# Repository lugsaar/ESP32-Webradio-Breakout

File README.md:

# ESP32-Webradio-SMT

This project is a basic board to build an ESP32 webradio. This is the very compact SMT variant. As an idea we used a
[blog article](https://www.az-delivery.de/blogs/azdelivery-blog-fur-arduino-und-raspberry-pi/internet-radio-mit-dem-esp32) 
of the company AZ-Delivery in March 2022. You will need some better SMT soldering skills.

## technical details

coming later

## current state

## maintained

- [Dominik](mailto:dominik@lug-saar.de) (LUG-Saar)
- [Manfred](mailto:mancas@lug-saar.de) (LUG-Saar)
- [Thomas](mailto:mase@setho.org) (TKS)

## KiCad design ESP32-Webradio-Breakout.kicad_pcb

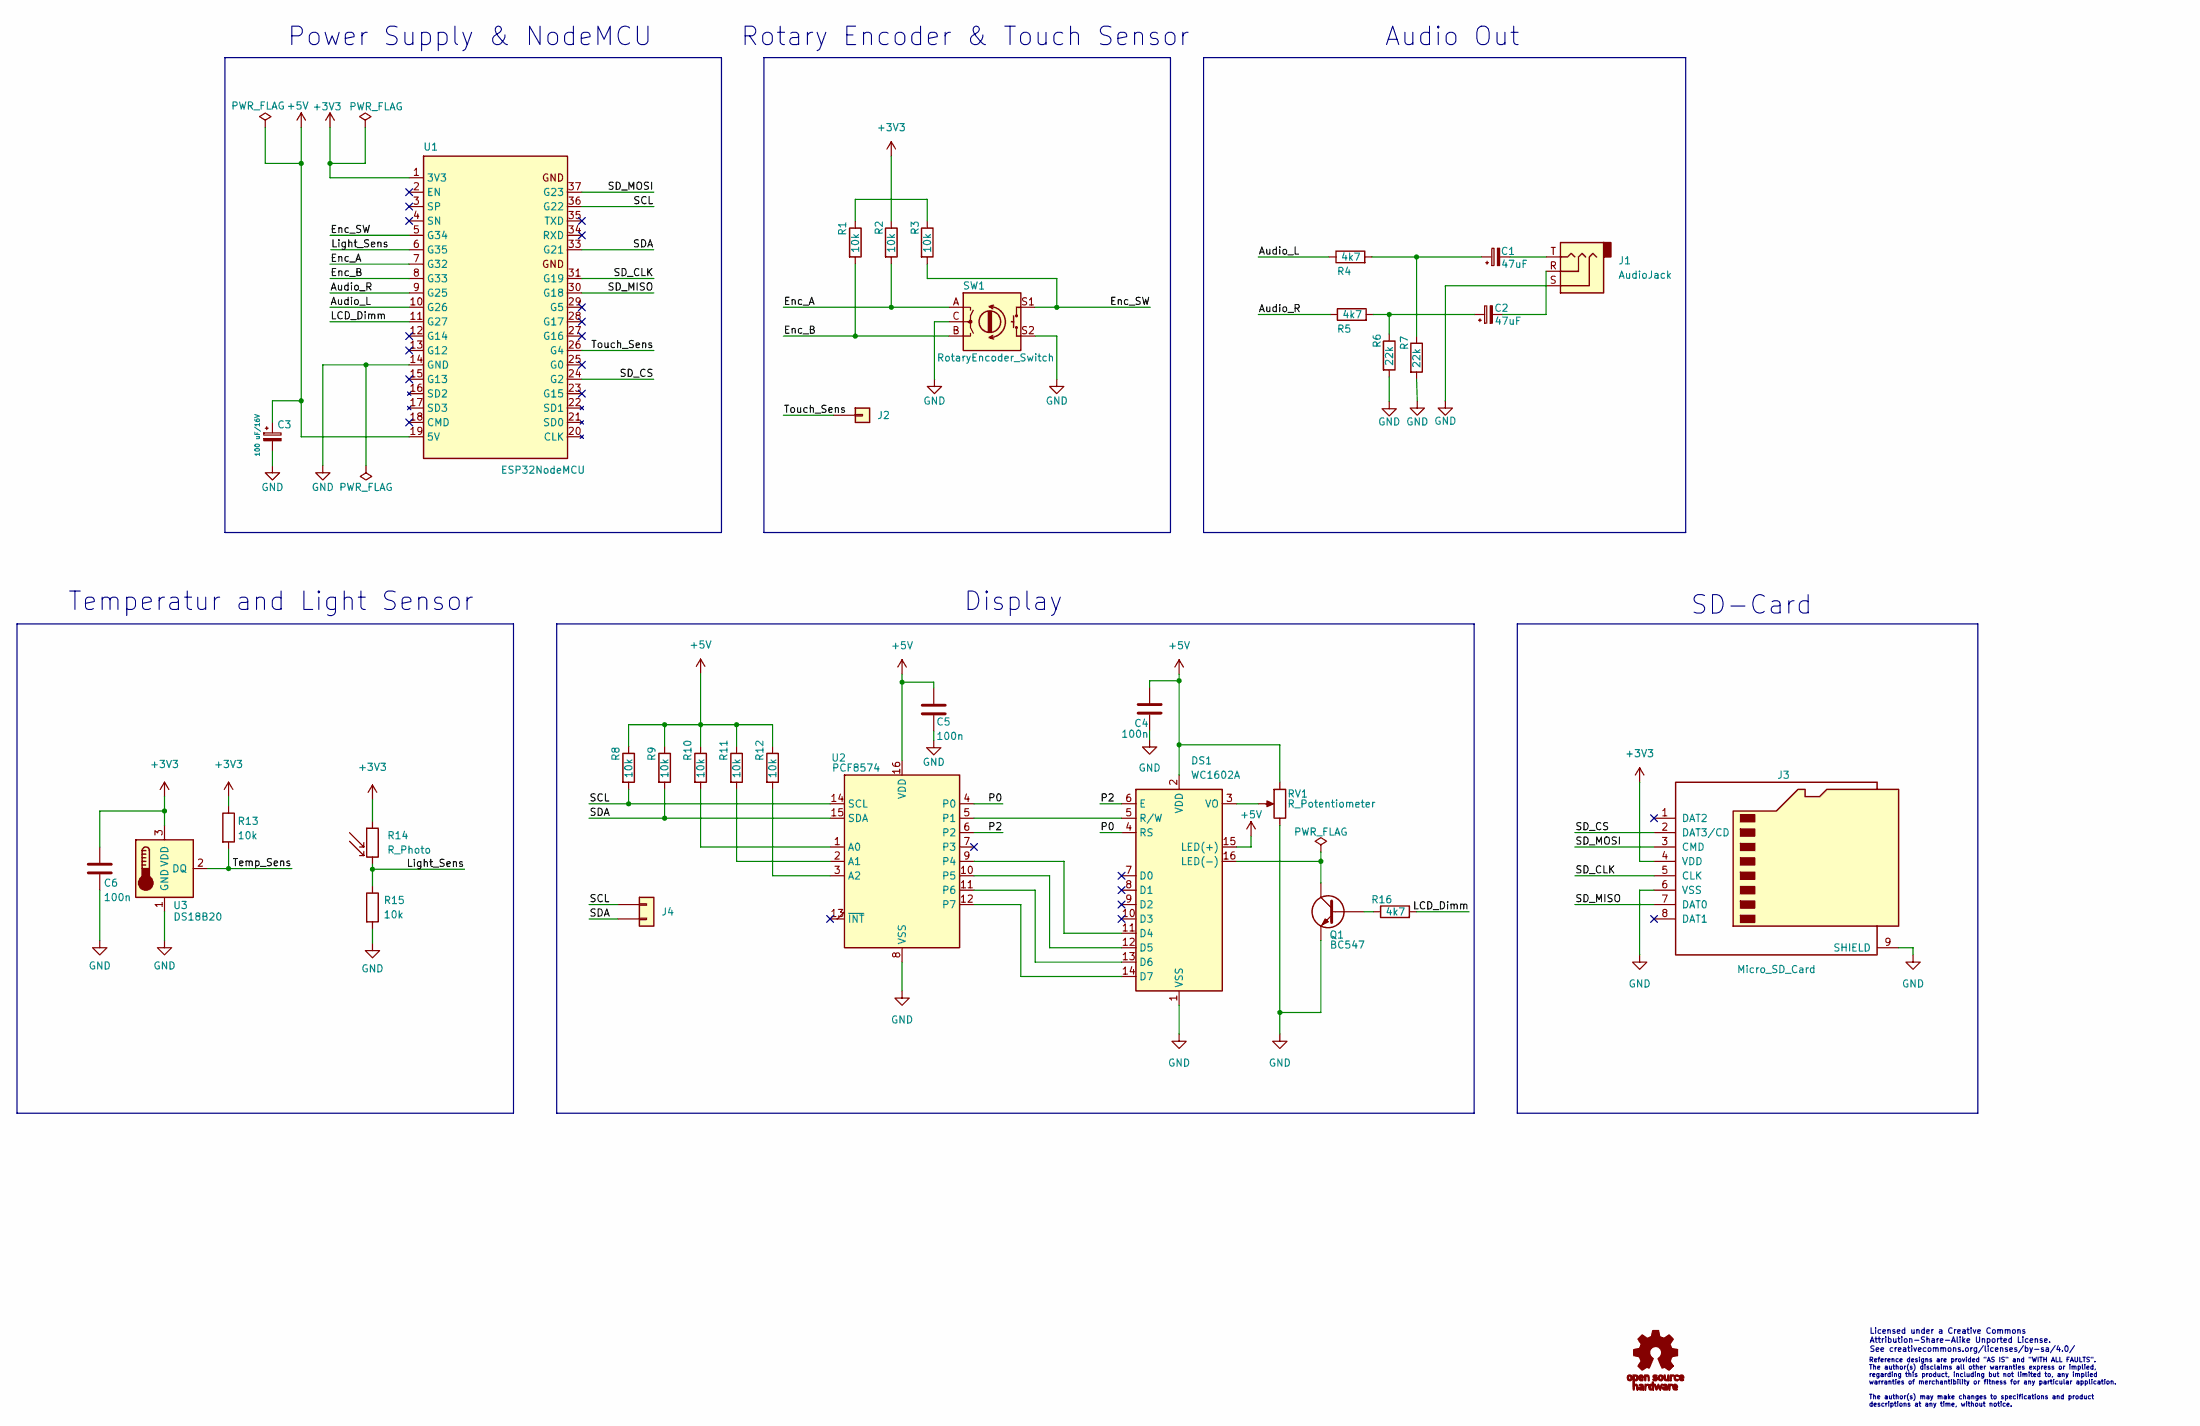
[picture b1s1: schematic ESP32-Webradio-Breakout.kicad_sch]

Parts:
C1, C2: 47uF; CP_Radial_D5.0mm_P2.50mm
C3: 100 uF/16V; CP_Radial_D6.3mm_P2.50mm
C4, C5, C6: 100n; C_Rect_L7.0mm_W3.5mm_P5.00mm
DS1: WC1602A; PinHeader_1x16_P2.54mm_Vertical
J1: AudioJack; Jack_3.5mm_CUI_SJ1-3533NG_Horizontal
J2: Conn_01x01; PinHeader_1x01_P2.54mm_Vertical
J3: Micro_SD_Card; PinHeader_1x08_P2.54mm_Vertical
J4: Conn_01x02; PinHeader_1x02_P2.54mm_Vertical
Q1: BC547; TO-92_Inline
R1, R2, R3, R8, R9, R10, R11, R12, R13, R15: 10k; R_Axial_DIN0207_L6.3mm_D2.5mm_P10.16mm_Horizontal
R4, R5, R16: 4k7; R_Axial_DIN0207_L6.3mm_D2.5mm_P10.16mm_Horizontal
R6, R7: 22k; R_Axial_DIN0207_L6.3mm_D2.5mm_P10.16mm_Horizontal
R14: R_Photo; R_LDR_5.1x4.3mm_P3.4mm_Vertical
RV1: R_Potentiometer; Potentiometer_ACP_CA9-V10_Vertical_Hole
SW1: RotaryEncoder_Switch; RotaryEncoder_Alps_EC11E-Switch_Vertical_H20mm
U1: ESP32NodeMCU; ESP32-NodeMCU_WROOM_32
U2: PCF8574; DIP-16_W10.16mm_LongPads
U3: DS18B20; TO-92_Inline

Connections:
+3V3: C6.1, J3.4 (VDD), R2.1, R13.1, R14.1, U1.1 (3V3), U3.3 (VDD)
+5V: C3.1, C4.1, C5.1, DS1.2 (VDD), DS1.15 (LED(+)), R8.1, R9.1, R10.1, R11.1, R12.1, RV1.1, U1.19 (5V), U2.16 (VDD)
/Audio_L: R4.1, U1.10 (G26)
/Audio_R: R5.1, U1.9 (G25)
/Enc_A: R2.2, SW1.A, U1.7 (G32)
/Enc_B: R1.2, SW1.B, U1.8 (G33)
/Enc_SW: R3.2, SW1.S1, U1.5 (G34)
/LCD_Dimm: R16.2, U1.11 (G27)
/Light_Sens: R14.2, R15.1, U1.6 (G35)
/P0: DS1.4 (RS), U2.4 (P0)
/P2: DS1.6 (E), U2.6 (P2)
/SCL: J4.1, R8.2, U1.36 (G22), U2.14 (SCL)
/SDA: J4.2, R9.2, U1.33 (G21), U2.15 (SDA)
/SD_CLK: J3.5 (CLK), U1.31 (G19)
/SD_CS: J3.2 (DAT3/CD), U1.24 (G2)
/SD_MISO: J3.7 (DAT0), U1.30 (G18)
/SD_MOSI: J3.3 (CMD), U1.37 (G23)
/Temp_Sens: R13.2, U3.2 (DQ)
/Touch_Sens: J2.1, U1.26 (G4)
GND: C3.2, C4.2, C5.2, C6.2, DS1.1 (VSS), J1.S, J3.6 (VSS), J3.9 (SHIELD), Q1.3 (E), R6.2, R7.2, R15.2, RV1.3, SW1.C, SW1.S2, U1.14 (GND), U1.32 (GND), U1.38 (GND), U2.8 (VSS), U3.1 (GND)
unnamed: C1.1, R4.2, R7.1
unnamed: C1.2, J1.T
unnamed: C2.1, R5.2, R6.1
unnamed: C2.2, J1.R
unnamed: DS1.3 (VO), RV1.2
unnamed: DS1.5 (R/W), U2.5 (P1)
unnamed: DS1.11 (D4), U2.9 (P4)
unnamed: DS1.12 (D5), U2.10 (P5)
unnamed: DS1.13 (D6), U2.11 (P6)
unnamed: DS1.14 (D7), U2.12 (P7)
unnamed: DS1.16 (LED(-)), Q1.1 (C)
unnamed: Q1.2 (B), R16.1
unnamed: R1.1, R3.1
unnamed: R10.2, U2.1 (A0)
unnamed: R11.2, U2.2 (A1)
unnamed: R12.2, U2.3 (A2)

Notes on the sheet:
Display
Licensed under a Creative Commons Attribution-Share-Alike Unported License. See creativecommons.org/licenses/by-sa/4.0/
Reference designs are provided "AS IS" and "WITH ALL FAULTS". The author(s) disclaims all other warranties express or implied, regarding this product, including but not limited to, any implied warranties of merchantibility or fitness for any particular application. The author(s) may make changes to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
Temperatur and Light Sensor
SD-Card
Power Supply & NodeMCU
Rotary Encoder & Touch Sensor
Audio Out

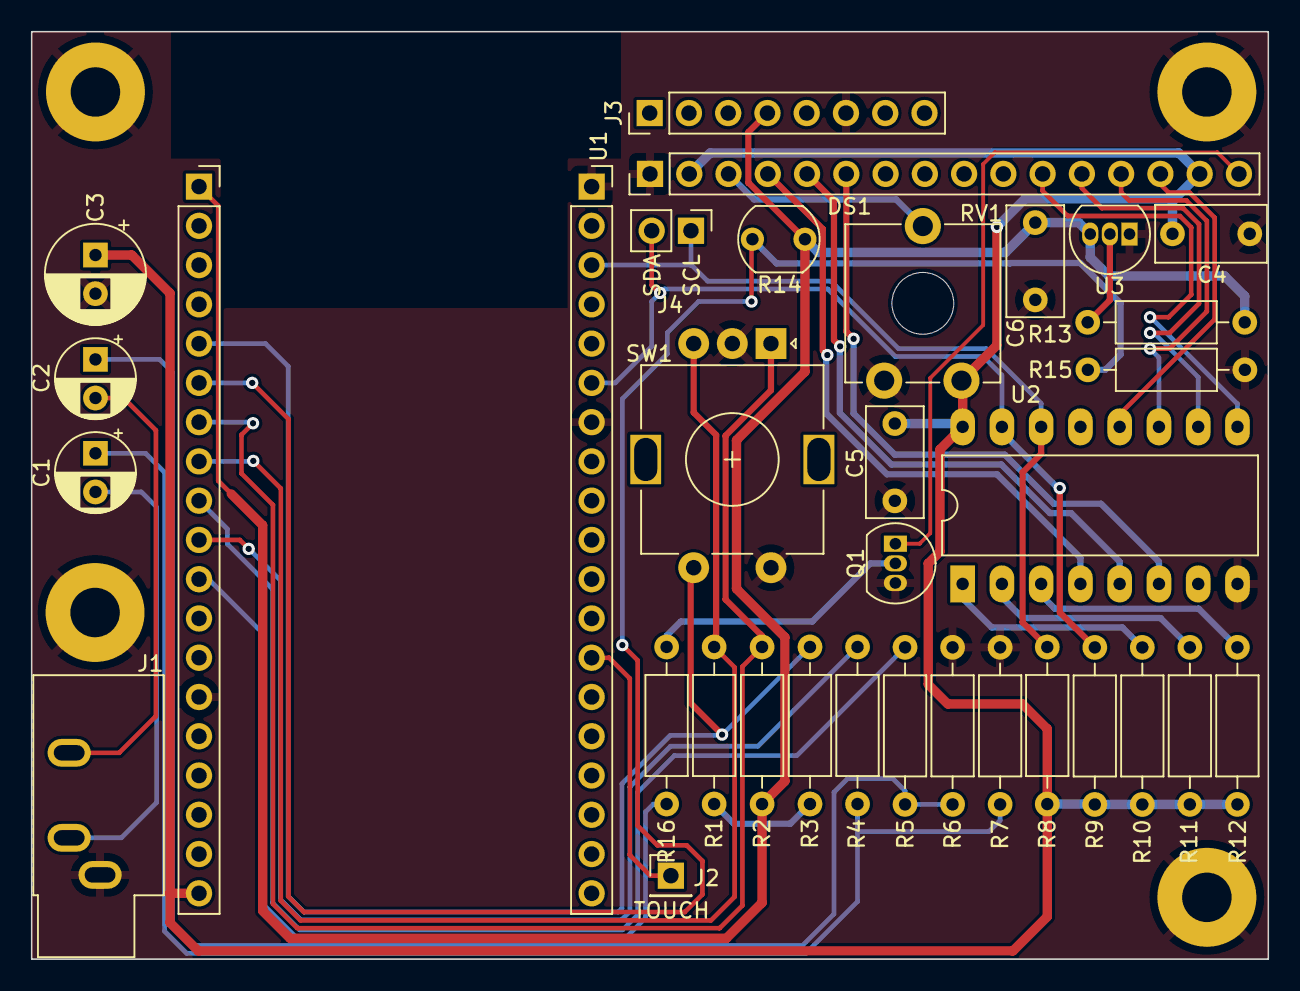
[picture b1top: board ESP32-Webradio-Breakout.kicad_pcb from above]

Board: 2 copper layers, 80.0 x 60.0 mm, 33 parts (0 on the bottom side), 36 nets.

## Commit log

2022-04-30 first init
2022-04-30 adding RCA Jack Connector to board
2022-05-07 adding ESP32-NodeMCU to Project Lib
2022-05-09 adding CC BY-SA 4.0 licens to the Project
2022-05-17 adding some Power Supply components
2022-05-21 Display and Remote 8-Bit I/O Expander for I2C added
2022-05-22 Adding 3D Model for Potentiometer ACP-CA9-V10
2022-05-23 Adding NPN-Transistor to switch the Backlight
2022-06-04 adding some mounting holes and README file
2022-06-06 Adding Temperatur and Light Sensor. ICs need 100n Cap and DS18B20 connecting to MCU
2022-06-06 Cleanup schematic before adding a new branch.
2022-06-07 Modified schematics for SMT Assigned footpronts for SMT Removed unneeded libraries Updated README
2022-06-07 Removed TH PCB
2022-06-07 Changed PCF8574A to PCF8574
2022-06-07 Added solder pads for I2C display
2022-06-07 adding 3D Model for Rotary Encoder
2022-06-09 Added electrolytic capacitor to 5V line
2022-06-09 Parts placement Updated README Updated Images
2022-06-09 Removed 24V supply
2022-06-09 Replaced Cinch Jacks by 3.5mm Jack New parts placement
2022-06-09 Removed cinch jacks from library
2022-06-09 Increased keepout area for wifi
2022-06-10 Regrouped NodeMCU
2022-06-11 Changed display and I2C connector footprint2 to pin header
2022-06-11 Rotated display connector 180 degrees
2022-06-11 Flipped left and right for a better display connection
2022-06-11 Parts placement top side
2022-06-11 Rotated C5 and C7
2022-06-11 Updated schematic pdf
2022-06-11 Added 3D model for rotary encoder
2022-06-12 Added pin for touch sensor Marked mounting holes as not in schematic
2022-06-12 Added pin for touch sensor Some regrouping
2022-06-13 Changed USB-C symbol Added 5k1 resistors for 5V handshake
2022-06-13 first routing
2022-06-15 Rotated display connector by 180 degrees
2022-06-18 routing first tracks
2022-06-21 routing
2022-06-29 Parts placement
2022-07-01 Added MicroSD cardreader
2022-07-01 Moved mounting hole out of keepout zone
2022-07-09 everything routed the first time, some ground connections still need to be done properly.
2022-07-19 Added MicroSD slot Changed footprints for I2C, temp_sens, light_sens and rotary encoder to solder pads New parts placement
2022-08-07 changing value of R6 and R7 to 22k. moving some tracks nicely
2022-10-04 connecting the microSD slot with MCU in the schematic via SPI

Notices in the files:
ESP32-Webradio-Breakout.kicad_sch:
© 2022 - 2023 LUG-Saar e.V., All rights reversed.
